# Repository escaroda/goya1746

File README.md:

<div>
  <picture>
    <source media="(prefers-color-scheme: light)" srcset="docs/logo_terein_light.svg">
    
  </picture>
</div>

## Overview

**goya1746** is an overdrive & preamp pedal based on the legendary Diezel VH4 channel 3. Fully open circuit board designed in KiCad 8. The main idea was to avoid oscillations on all gain levels. This project is shared for hobbyists who want to study, modify, or build their own. The full PCB outline is 115 × 70 mm (4.53 × 2.76 in), but the usable area is about 96 × 70 mm (3.78 × 2.76 in) if you remove the side "wings" in KiCad and define your own edge cut before generating Gerbers. In theory, it should fit a 1590BB enclosure, but keep in mind that each potentiometer is wired separately and the connection pads are not located at the corners of the PCB, so there will be quite a lot of wiring inside.

## Manufacturing

Check [Releases](https://github.com/escaroda/goya1746/releases) page for `.zip` Gerber files ready for production.
If you want to fabricate the PCB, just upload the `.zip` Gerber files to your favorite board house (e.g. JLCPCB, PCBWay, NEXTPCB). Make sure you can source all components in the correct form factor before manufacturing the board.

## Important notes

- This pedal should be powered with 12-18VDC. Power draw 100mA. There are claims that 15VDC provides the best results because it generates less heat in the voltage regulator, but 18VDC is the standard.
- The LM2940 regulator is installed vertically. Its metal tab can be mounted to the chassis to help dissipate heat — just make sure the chassis is grounded and not connected to any other signal paths. This workaround increases build complexity and will be refined in a future revision. The goal was to minimize board temperature to prolong the lifespan of nearby electrolytic capacitors.
- Only five electrolytic capacitors are used, and they are strategically placed to provide shielding for the TC1044SCPA charge pump switching regulator IC from nearby components.
- Some capacitors, specifically C3, C4, C5, C9, C12, C17, C18, C20 and C22, that were originally electrolytic, have been replaced with film capacitors. The schematic remains unchanged, but the PCB footprints are different. You can still install electrolytic capacitors in those positions, but be sure to observe the correct polarity. Future revisions will return to electrolytic capacitors because they're cheaper and the experiment didn't produce a better tone.
- The resistor 2.2K 1/4W for the LED 12V should be placed on the wire that connects it to the PCB. Adjust the resistor value to achieve the desired brightness.
- Even though the LM2940CT-12/NOPB voltage regulator provides reverse-polarity protection for the entire circuit, it is still good practice to solder a 1N5817 Schottky diode in series with the + wire leading to the DC input. The striped end (cathode) should face the PCB. For example: DC Jack → [Anode — Diode — Cathode] → PCB. You can see this approach used in almost all PedalPCB schematics. Make sure you identify the +V and Ground pins of the DC input by referring to the PCB design in KiCad.
- For experimental purposes, the mid-pot tone control is wired in the so-called "Marshall style," which gives the mid control a stronger effect and shifts the tone toward a punchier, more mid-rich sound compared to a "Fender style" tone stack. To switch back to the "Fender style" configuration, connect pins 2 and 3 of the MID potentiometer together.
- Because of space limitations in this version, buffered bypass solder pads are not included. This may be added in a future revision. At the moment, the on/off switch must be wired as a true bypass by the builder. Or, if you're feeling hacky, you can connect a wire between the C3 capacitor and the R4 resistor (for example, to the side of the R4 resistor that isn't connected to Ground), and that will be your buffer. And the signal after R17 should be shorted to Ground during bypass.

P.S. Future releases are not expected in the near term due to financial constraints. However, once the situation improves, development will continue, including projects such as Turbo Rat, SansAmp GT-2, Boss CE-2, as well as a search for the best fuzz circuit.

## Acknowledgments

- [Diezel](https://www.diezelamplification.com/artist/) for inspiring design of modern high-gain amplifiers.
- [freestompboxes.org](https://www.freestompboxes.org/viewtopic.php?t=28011) and its community — without their prior work, this project would not have been possible.
- [pedalpcb.com](https://www.pedalpcb.com/product/valhalla/) DIY shop, for inspiration and clear, easy-to-understand schematics.
- [aionfx.com](https://aionfx.com/project/dz4-preamp/) for showing how things can be changed.
- [pcbguitarmania.com](https://pcbguitarmania.com/product/benzin-vh4/) for yet another reference and food for thoughts.
- [effectslayouts.blogspot.com](https://effectslayouts.blogspot.com/2019/07/diezel-vh4.html) for better understanding how the footswitch wiring should work.
- [techexplorations.com](https://techexplorations.com/kicad/) for great KiCad educational materials.
- [Hans Rosenberg](https://www.youtube.com/@HansRosenberg74/videos) for interesting talks about good PCB design in general.

## Guides

These guides might help beginners who have never built their own pedals. Some links might become broken.

- [Gray Bench Electronics - Full Kit Build Video](https://www.youtube.com/watch?v=_JjrbrLn0x4)
- [RUDE TECH - Guitar Effect Pedal Kit Build Instructions Video](https://www.youtube.com/watch?v=ZrMTKuxQ1Xw)
- [pedalparts.co.uk - General Build Guide PDF](https://pedalparts.co.uk/docs/GeneralBuildGuide.pdf)
- [five-cats-pedals.co.uk - General Build Guide PDF](https://www.five-cats-pedals.co.uk/wp-content/uploads/2022/09/FiveCatsPedals-General-Build-Guide-V1.1-Aug-2022.pdf)
- [aionfx.com - Troubleshooting Guide PDF](https://aionfx.com/app/files/docs/kit_troubleshooting_guide.pdf)
- [masfx.io - A Guide to Build Your Own DIY Guitar Pedal PDF](https://masfx.io/quickfuzz.pdf)
- [guitarpcb.com - A Beginner's Guide to Effects Pedals Components PDF](https://guitarpcb.com/wp-content/uploads/2018/07/A-Beginners-Guide-to-Components.pdf)
- [premierguitar.com - Build Your Own Stompbox PDF](https://roar-assets-auto.rbl.ms/documents/9051/Oct14_PGDistortion_BuildGuide_Final_R2.pdf)

## Bill of Materials

All resistors are 1/4 W metal film with 1% tolerance. All capacitors must have a minimum voltage rating of 35 V. Consider capacitors to be polypropylene film unless otherwise specified. If 25 kΩ potentiometers are unavailable, a 50 kΩ potentiometer may be used together with a 50 kΩ resistor in parallel. This changes the taper slightly (especially for log pots), because the resistance curve is altered by the parallel resistor. Ferrite bead R1 is optional and can be replaced with a wire link. The OPA2134 at U1 may be substituted with another TL072 without any noticeable difference.

You'll also need:
- 6.3 mm jack sockets,
- DIP8 sockets for each op-amp and a charge pump,
- optional JST connectors for DC input and LED,
- a **plastic** DC input jack wired for center negative.

This pedal provides two output options: Guitar Out and Power Out. In most cases, you won't need to wire both. If the pedal is used at the end of a signal chain (similar to a real amplifier), Power Out is the preferred choice. Power Out is a low-impedance, line-level signal, so it can be safely connected to standard line inputs, such as those on audio interface. Guitar Out is a traditional high-impedance output suitable for connecting to other pedals or amp inputs.

*For ICs and other essential components, use reputable suppliers only. Avoid sources like eBay or AliExpress, as counterfeit or unreliable parts are widespread on those platforms and may cause malfunction or failure.*

|Reference          |Value           |Qty|Notes                                           |
|-------------------|----------------|---|------------------------------------------------|
|BASS1              |A1M             |1  |                                                |
|C1,C7,C15,C16      |22n             |4  |                                                |
|C2,C6,C13          |100p            |3  |Ceramic Disc                                    |
|C3,C4,C5,C17       |1u              |4  |                                                |
|C8                 |2n2             |1  |                                                |
|C23                |2n2             |1  |Ceramic Disc or Film                            |
|C9,C12,C18         |2u2             |3  |                                                |
|C10                |47p             |1  |Ceramic Disc                                    |
|C11                |4n7             |1  |                                                |
|C14                |560p            |1  |Ceramic Disc                                    |
|C19                |330n            |1  |                                                |
|C20,C22            |10u             |2  |                                                |
|C21                |1n              |1  |Ceramic Disc or Film                            |
|C24,C25,C26,C27,C28|47u             |5  |Electrolytic ~35V                               |
|D1,D2,D5,D6        |1N4148          |4  |Signal diode, DO-35                             |
|D3,D4              |1N4734A         |2  |5.6V zener (equivalents: 1N752, 1N5232), DO-41  |
|D7                 |LED 12V         |1  |Require ~2.2K resistor                          |
|J1                 |GUITAR INPUT    |1  |                                                |
|J2                 |DC INPUT        |1  |                                                |
|J3                 |POWER OUT       |1  |                                                |
|J4                 |GUITAR OUT      |1  |                                                |
|R1                 |FerriteBead     |1  |Optional                                        |
|R2,R3,R14          |1M              |3  |                                                |
|R4,R5,R15,R25,R37  |100K            |5  |                                                |
|R6,R13,R18,R33     |10K             |4  |                                                |
|R7,R10,R11,R17,R19 |220K            |5  |                                                |
|R8,R16             |470K            |2  |                                                |
|R9                 |680K            |1  |                                                |
|R20                |39K             |1  |                                                |
|R24                |1M5             |1  |                                                |
|R26,R34            |1K              |2  |                                                |
|R28                |100R            |1  |                                                |
|R30                |47R             |1  |                                                |
|R31                |56K             |1  |                                                |
|R32                |4K7             |1  |                                                |
|R36                |150K            |1  |                                                |
|R38,R39            |10R             |2  |                                                |
|U1                 |OPA2134         |1  |Dual op-amp, DIP8. May be substituted with TL072|
|U2,U3              |TL072           |2  |Dual op-amp, DIP8                               |
|IC4                |LM2940CT-12_NOPB|1  |Low-dropout voltage regulator +12V              |
|IC100              |TC1044SCPA      |1  |Charge Pump IC, DIP8                            |
|DEEP1,PRES1        |C25K            |2  |                                                |
|GAIN1              |A250K           |1  |                                                |
|MID1               |B25K            |1  |                                                |
|TREBLE1            |B250K           |1  |                                                |
|VOL1               |A10K            |1  |                                                |

## Ground & Shielding

The chassis should be properly grounded to ensure effective shielding and noise reduction. Where possible, use cables with an outer braided shield and connect the shield to ground at least on one end — preferably at the PCB side. The metal backs of potentiometers may also be connected to ground to help reduce noise pickup through their housings. Ground loops are generally not a concern inside a small enclosure such as a pedal, so a strict star-ground topology is unnecessary. The **DC input jack must be plastic** (isolated from the enclosure). Most pedals use a negative center power supply, so a metal jack touching the chassis could short the positive voltage to ground.

As a side note. There are a lot of myths and misconceptions about grounding in PCB design, mostly because of the many variables that need to be considered together with each statement. At some point, you think you understand how it works, but then you realize you don't. It's not always clear what the real cause of a problem is, and fixing one issue can accidentally fix another, leading to false conclusions.

For example, advanced grounding techniques are mainly used for high-frequency applications, and the effects are often negligible in the audio range (up to 20 kHz). Through-hole components are considered obsolete for high-frequency PCBs, yet they are abundant in most analog music equipment. If we start replacing everything with SMD components, we might lose some of the unique characteristics that contribute to the sound we expect, or just our own perception might change.

And let's not forget that the sound we're looking for doesn't always have to be perfect — it just has to be pleasant to our ears. Who wants to listen to a perfectly clean sine wave, right? We enjoy it when it's mixed with other harmonics and subtle modulations that make the sound feel alive. Often, it's exactly those imperfections in the components and PCB layout that create the desired effect.

## PCB Specifications

- Layers: 2
- Thickness: 1.6 mm
- PCB Size: 115 x 70 mm (4.53 × 2.76 in)
- Copper weight: 1 oz (default PCB fab)
- Trace clearance: 6 mil or 0.1524mm
- Soldermask: [Black / Green / Anything]
- Silkscreen: [White]
- Surface finish: HASL
- Material: FR-4
- Via finish: Tented
- Min. Drill Hole: 0.3 mm
- Assembly: Through-hole components only (no SMD)

## Recommended Fabricators
- NEXTPCB
- JLCPCB
- PCBWay

## Gallery

## TODO

- Add a connection pad for the buffered output between C3 and R4, and find a suitable location for it on the PCB. Add a connection pad after R17 to be able to short it to Ground during bypass. Update schematic.
- Make configuration where all caps are the same type as in Diezel VH4 pedal since any difference could affect the tone.
- Add + signs on a silkscreen layer for all connection pads to lower the risk of mistakes.
- Position the voltage regulator so that it can be laid flat on the PCB. Add a ground plane underneath it for better heat distribution.
- Consider adapting the PCB layout to fit more popular enclosures, such as 1590BB.
- Would it be possible to rewire everything so that pots connected directly to the PCB? Estimate PCB size, production costs and a headache of acquiring the correct pots.

## License

This hardware design is distributed under the MIT License.
Copyright (c) 2025 Dmitry Escaroda.

## Contribution

If you build this pedal, feel free to share photos or mods via Discussions. If you are an experienced Electronics Engineer or PCB Designer and see how something could be improved for the benefit of all, please submit an issue.

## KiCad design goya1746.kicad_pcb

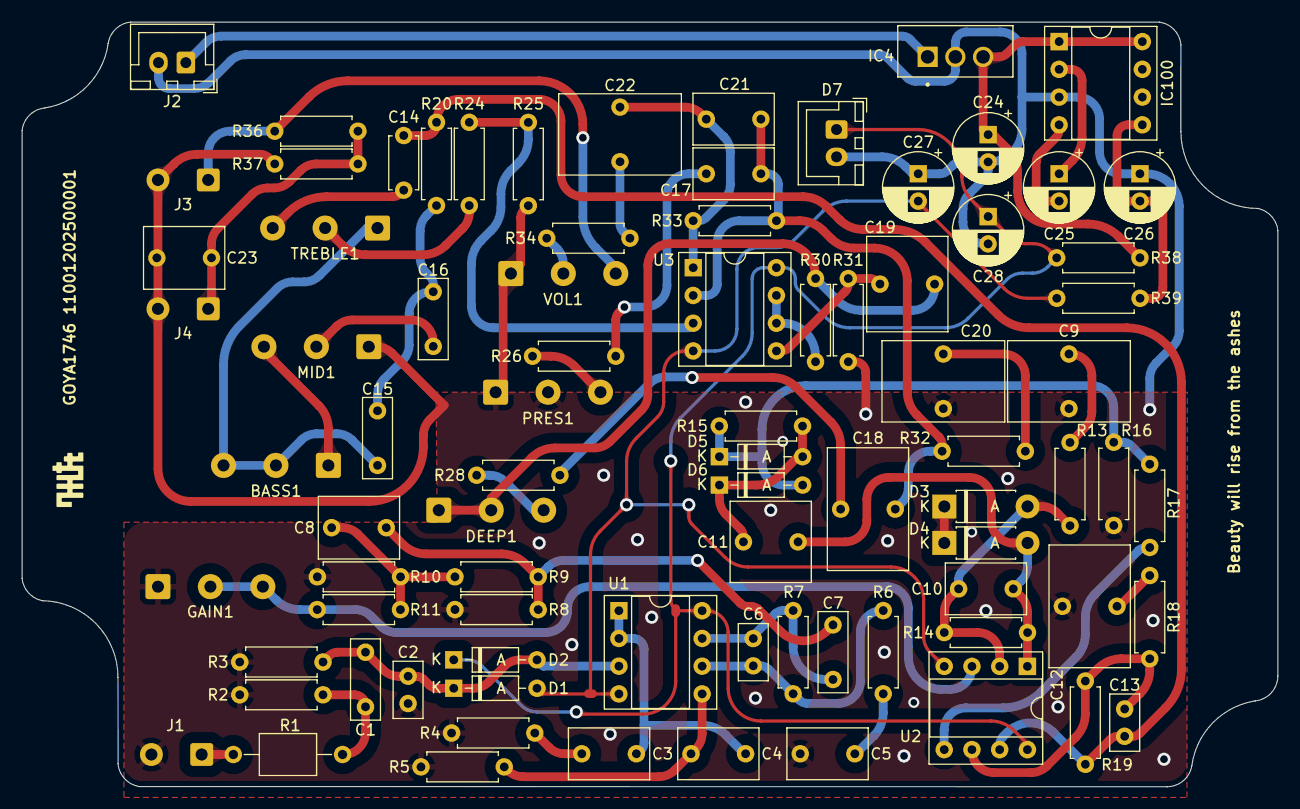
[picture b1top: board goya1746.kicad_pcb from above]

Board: 2 copper layers, 115.0 x 70.0 mm, 83 parts (0 on the bottom side), 51 nets.

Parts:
BASS1: A1M; SolderWire-0.5sqmm_1x03_P4.8mm_D0.9mm_OD2.3mm
C1, C7, C15, C16: 22n; C_Rect_L7.2mm_W2.5mm_P5.00mm_FKS2_FKP2_MKS2_MKP2
C2, C6, C13: 100p; C_Disc_D5.0mm_W2.5mm_P2.50mm
C3, C4, C5, C17: 1u; C_Rect_L7.2mm_W4.5mm_P5.00mm_FKS2_FKP2_MKS2_MKP2
C8, C23: 2n2; C_Rect_L7.2mm_W5.5mm_P5.00mm_FKS2_FKP2_MKS2_MKP2
C9, C12, C18: 2u2; C_Rect_L7.2mm_W11.0mm_P5.00mm_FKS2_FKP2_MKS2_MKP2
C10: 47p; C_Rect_L7.2mm_W4.5mm_P5.00mm_FKS2_FKP2_MKS2_MKP2
C11: 4n7; C_Rect_L7.2mm_W7.2mm_P5.00mm_FKS2_FKP2_MKS2_MKP2
C14: 560p; C_Disc_D4.7mm_W2.5mm_P5.00mm
C19: 330n; C_Rect_L7.2mm_W8.5mm_P5.00mm_FKP2_FKP2_MKS2_MKP2
C20, C22: 10u; C_Rect_L7.2mm_W11.0mm_P5.00mm_FKS2_FKP2_MKS2_MKP2
C21: 1n; C_Rect_L7.2mm_W4.5mm_P5.00mm_FKS2_FKP2_MKS2_MKP2
C24, C25, C26, C27, C28: 47u; CP_Radial_D6.3mm_P2.50mm
D1, D2, D5, D6: 1N4148; D_DO-35_SOD27_P7.62mm_Horizontal
D3, D4: 1N4734A; D_DO-41_SOD81_P7.62mm_Horizontal
D7: LED 12V; JST_XH_B2B-XH-A_1x02_P2.50mm_Vertical
DEEP1: C25K; SolderWire-0.5sqmm_1x03_P4.8mm_D0.9mm_OD2.3mm
GAIN1: A250K; SolderWire-0.5sqmm_1x03_P4.8mm_D0.9mm_OD2.3mm
IC4: LM2940CT-12_NOPB; TO254P1054X470X1955-3
IC100: TC1044SCPA; DIP-8_W7.62mm_Socket
J1: GUITAR INPUT; SolderWire-0.5sqmm_1x02_P4.6mm_D0.9mm_OD2.1mm
J2: DC INPUT; JST_XH_B2B-XH-A_1x02_P2.50mm_Vertical
J3: POWER OUT; SolderWire-0.5sqmm_1x02_P4.6mm_D0.9mm_OD2.1mm
J4: GUITAR OUT; SolderWire-0.5sqmm_1x02_P4.6mm_D0.9mm_OD2.1mm
MID1: B25K; SolderWire-0.5sqmm_1x03_P4.8mm_D0.9mm_OD2.3mm
PRES1: C25K; SolderWire-0.5sqmm_1x03_P4.8mm_D0.9mm_OD2.3mm
R1: FerriteBead; L_Axial_L5.0mm_D3.6mm_P10.00mm_Horizontal_Murata_BL01RN1A2A2
R2, R3, R14: 1M; R_Axial_DIN0207_L6.3mm_D2.5mm_P7.62mm_Horizontal
R4, R5, R15, R25, R37: 100K; R_Axial_DIN0207_L6.3mm_D2.5mm_P7.62mm_Horizontal
R6, R13, R18, R33: 10K; R_Axial_DIN0207_L6.3mm_D2.5mm_P7.62mm_Horizontal
R7, R10, R11, R17, R19: 220K; R_Axial_DIN0207_L6.3mm_D2.5mm_P7.62mm_Horizontal
R8, R16: 470K; R_Axial_DIN0207_L6.3mm_D2.5mm_P7.62mm_Horizontal
R9: 680K; R_Axial_DIN0207_L6.3mm_D2.5mm_P7.62mm_Horizontal
R20: 39K; R_Axial_DIN0207_L6.3mm_D2.5mm_P7.62mm_Horizontal
R24: 1M5; R_Axial_DIN0207_L6.3mm_D2.5mm_P7.62mm_Horizontal
R26, R34: 1K; R_Axial_DIN0207_L6.3mm_D2.5mm_P7.62mm_Horizontal
R28: 100R; R_Axial_DIN0207_L6.3mm_D2.5mm_P7.62mm_Horizontal
R30: 47R; R_Axial_DIN0207_L6.3mm_D2.5mm_P7.62mm_Horizontal
R31: 56K; R_Axial_DIN0207_L6.3mm_D2.5mm_P7.62mm_Horizontal
R32: 4K7; R_Axial_DIN0207_L6.3mm_D2.5mm_P7.62mm_Horizontal
R36: 150K; R_Axial_DIN0207_L6.3mm_D2.5mm_P7.62mm_Horizontal
R38, R39: 10R; R_Axial_DIN0207_L6.3mm_D2.5mm_P7.62mm_Horizontal
TREBLE1: B250K; SolderWire-0.5sqmm_1x03_P4.8mm_D0.9mm_OD2.3mm
U1: OPA2134; DIP-8_W7.62mm_Socket
U2, U3: TL072; DIP-8_W7.62mm_Socket
VOL1: A10K; SolderWire-0.5sqmm_1x03_P4.8mm_D0.9mm_OD2.3mm

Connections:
+12V: C28.1, D2.1 (K), D7.1, R38.1, U1.8 (V+), U2.8 (V+), U3.8 (V+)
-12V: C27.2, D1.2 (A), R39.1, U1.4 (V-), U2.4 (V-), U3.4 (V-)
GND: C2.1, C5.2, C9.2, C12.2, C20.2, C23.2, C24.2, C26.1, C27.1, C28.2, D7.2, GAIN1.1, IC4.2 (GND), IC100.3 (GND), J1.2, J2.2, J3.2, J4.2, MID1.1, PRES1.1, PRES1.2, R2.2, R3.2, R4.2, R5.2, R8.2, R10.2, R16.1, R25.1, R31.1, R37.1, VOL1.1
unnamed: BASS1.1, MID1.3
unnamed: BASS1.2, BASS1.3, C15.1, TREBLE1.1
unnamed: C1.1, R1.2, R2.1
unnamed: C3.2, R4.1
unnamed: C5.1, R6.1
unnamed: C6.1, C7.2, R7.2, U1.7
unnamed: C7.1, C8.2, R8.1, R9.1
unnamed: C8.1, R9.2, R10.1, R11.1
unnamed: C9.1, R13.1
unnamed: C12.1, R18.2
unnamed: C13.1, C14.2, R19.1, R20.1, U2.7
unnamed: C14.1, TREBLE1.3
unnamed: C15.2, C16.2, R20.2
unnamed: C16.1, MID1.2
unnamed: C17.2, R26.2
unnamed: C18.2, R28.1
unnamed: C19.1, DEEP1.1, DEEP1.2, R30.2
unnamed: C20.1, R32.2
unnamed: C21.1, C22.1, R33.1, U3.1
unnamed: C22.2, R34.1
unnamed: C1.2, C2.2, D1.1 (K), D2.2 (A), R3.1, U1.3 (+)
unnamed: C10.2, D3.2 (A), R13.2, R14.1, U2.2 (-)
unnamed: D3.1 (K), D4.1 (K)
unnamed: C10.1, C11.2, D4.2 (A), R14.2, U2.1
unnamed: C11.1, D5.2 (A), D6.1 (K), R15.1
unnamed: D5.1 (K), D6.2 (A), R15.2, R16.2, R17.2
unnamed: DEEP1.3, R28.2
unnamed: IC4.1 (IN), J2.1
unnamed: C24.1, IC4.3 (OUT), IC100.1 (BOOST), IC100.8 (V+), R38.2
unnamed: C25.1, IC100.2 (CAP+)
unnamed: C25.2, IC100.4 (CAP-)
unnamed: C26.2, IC100.5 (VOUT), R39.2
unnamed: J1.1, R1.1
unnamed: J3.1, R36.1, VOL1.3
unnamed: C23.1, J4.1, R36.2, R37.2
unnamed: PRES1.3, R26.1
unnamed: R24.1, TREBLE1.2
unnamed: R34.2, VOL1.2
unnamed: C3.1, C4.1, U1.1, U1.2 (-)
unnamed: C4.2, R5.1, U1.5 (+)
unnamed: C6.2, R6.2, R7.1, U1.6 (-)
unnamed: GAIN1.2, GAIN1.3, R11.2, U2.3 (+)
unnamed: R17.1, U2.5 (+)
unnamed: C13.2, R18.1, R19.2, U2.6 (-)
unnamed: R24.2, R25.2, U3.3 (+)
unnamed: C17.1, C18.1, C21.2, R32.1, R33.2, U3.2 (-)
unnamed: C19.2, R31.2, U3.5 (+)
unnamed: R30.1, U3.6 (-), U3.7

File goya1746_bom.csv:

Reference	Value	Datasheet	Footprint	Qty	DNP
BASS1	A1M	~	Connector_Wire:SolderWire-0.5sqmm_1x03_P4.8mm_D0.9mm_OD2.3mm	1	
C1,C7,C15,C16	22n	~	Capacitor_THT:C_Rect_L7.2mm_W2.5mm_P5.00mm_FKS2_FKP2_MKS2_MKP2	4	
C2,C6,C13	100p	~	Capacitor_THT:C_Disc_D5.0mm_W2.5mm_P2.50mm	3	
C3,C4,C5,C17	1u	~	Capacitor_THT:C_Rect_L7.2mm_W4.5mm_P5.00mm_FKS2_FKP2_MKS2_MKP2	4	
C8,C23	2n2	~	Capacitor_THT:C_Rect_L7.2mm_W5.5mm_P5.00mm_FKS2_FKP2_MKS2_MKP2	2	
C9,C12,C18	2u2	~	Capacitor_THT:C_Rect_L7.2mm_W11.0mm_P5.00mm_FKS2_FKP2_MKS2_MKP2	3	
C10	47p	~	Capacitor_THT:C_Rect_L7.2mm_W4.5mm_P5.00mm_FKS2_FKP2_MKS2_MKP2	1	
C11	4n7	~	Capacitor_THT:C_Rect_L7.2mm_W7.2mm_P5.00mm_FKS2_FKP2_MKS2_MKP2	1	
C14	560p	~	Capacitor_THT:C_Disc_D4.7mm_W2.5mm_P5.00mm	1	
C19	330n	~	Capacitor_THT:C_Rect_L7.2mm_W8.5mm_P5.00mm_FKP2_FKP2_MKS2_MKP2	1	
C20,C22	10u	~	Capacitor_THT:C_Rect_L7.2mm_W11.0mm_P5.00mm_FKS2_FKP2_MKS2_MKP2	2	
C21	1n	~	Capacitor_THT:C_Rect_L7.2mm_W4.5mm_P5.00mm_FKS2_FKP2_MKS2_MKP2	1	
C24,C25,C26,C27,C28	47u	~	Capacitor_THT:CP_Radial_D6.3mm_P2.50mm	5	
D1,D2,D5,D6	1N4148	~	Diode_THT:D_DO-35_SOD27_P7.62mm_Horizontal	4	
D3,D4	1N4734A	~	Diode_THT:D_DO-41_SOD81_P7.62mm_Horizontal	2	
D7	LED 12V	~	Connector_JST:JST_XH_B2B-XH-A_1x02_P2.50mm_Vertical	1	
DEEP1,PRES1	C25K	~	Connector_Wire:SolderWire-0.5sqmm_1x03_P4.8mm_D0.9mm_OD2.3mm	2	
GAIN1	A250K	~	Connector_Wire:SolderWire-0.5sqmm_1x03_P4.8mm_D0.9mm_OD2.3mm	1	
IC4	LM2940CT-12_NOPB		LM2940CT12NOPB:TO254P1054X470X1955-3	1	
IC100	TC1044SCPA		Package_DIP:DIP-8_W7.62mm_Socket	1	
J1	GUITAR INPUT	~	Connector_Wire:SolderWire-0.5sqmm_1x02_P4.6mm_D0.9mm_OD2.1mm	1	
J2	DC INPUT	~	Connector_JST:JST_XH_B2B-XH-A_1x02_P2.50mm_Vertical	1	
J3	POWER OUT	~	Connector_Wire:SolderWire-0.5sqmm_1x02_P4.6mm_D0.9mm_OD2.1mm	1	
J4	GUITAR OUT	~	Connector_Wire:SolderWire-0.5sqmm_1x02_P4.6mm_D0.9mm_OD2.1mm	1	
MID1	B25K	~	Connector_Wire:SolderWire-0.5sqmm_1x03_P4.8mm_D0.9mm_OD2.3mm	1	
R1	FerriteBead	~	Inductor_THT:L_Axial_L5.0mm_D3.6mm_P10.00mm_Horizontal_Murata_BL01RN1A2A2	1	
R2,R3,R14	1M	~	Resistor_THT:R_Axial_DIN0207_L6.3mm_D2.5mm_P7.62mm_Horizontal	3	
R4,R5,R15,R25,R37	100K	~	Resistor_THT:R_Axial_DIN0207_L6.3mm_D2.5mm_P7.62mm_Horizontal	5	
R6,R13,R18,R33	10K	~	Resistor_THT:R_Axial_DIN0207_L6.3mm_D2.5mm_P7.62mm_Horizontal	4	
R7,R10,R11,R17,R19	220K	~	Resistor_THT:R_Axial_DIN0207_L6.3mm_D2.5mm_P7.62mm_Horizontal	5	
R8,R16	470K	~	Resistor_THT:R_Axial_DIN0207_L6.3mm_D2.5mm_P7.62mm_Horizontal	2	
R9	680K	~	Resistor_THT:R_Axial_DIN0207_L6.3mm_D2.5mm_P7.62mm_Horizontal	1	
R20	39K	~	Resistor_THT:R_Axial_DIN0207_L6.3mm_D2.5mm_P7.62mm_Horizontal	1	
R24	1M5	~	Resistor_THT:R_Axial_DIN0207_L6.3mm_D2.5mm_P7.62mm_Horizontal	1	
R26,R34	1K	~	Resistor_THT:R_Axial_DIN0207_L6.3mm_D2.5mm_P7.62mm_Horizontal	2	
R28	100R	~	Resistor_THT:R_Axial_DIN0207_L6.3mm_D2.5mm_P7.62mm_Horizontal	1	
R30	47R	~	Resistor_THT:R_Axial_DIN0207_L6.3mm_D2.5mm_P7.62mm_Horizontal	1	
R31	56K	~	Resistor_THT:R_Axial_DIN0207_L6.3mm_D2.5mm_P7.62mm_Horizontal	1	
R32	4K7	~	Resistor_THT:R_Axial_DIN0207_L6.3mm_D2.5mm_P7.62mm_Horizontal	1	
R36	150K	~	Resistor_THT:R_Axial_DIN0207_L6.3mm_D2.5mm_P7.62mm_Horizontal	1	
R38,R39	10R	~	Resistor_THT:R_Axial_DIN0207_L6.3mm_D2.5mm_P7.62mm_Horizontal	2	
TREBLE1	B250K	~	Connector_Wire:SolderWire-0.5sqmm_1x03_P4.8mm_D0.9mm_OD2.3mm	1	
U1	OPA2134	http://www.ti.com/lit/ds/symlink/opa134.pdf	Package_DIP:DIP-8_W7.62mm_Socket	1	
U2,U3	TL072	http://www.ti.com/lit/ds/symlink/tl071.pdf	Package_DIP:DIP-8_W7.62mm_Socket	2	
VOL1	A10K	~	Connector_Wire:SolderWire-0.5sqmm_1x03_P4.8mm_D0.9mm_OD2.3mm	1

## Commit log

2025-10-24 Init
2025-10-24 Fix Readme
2025-10-25 Readme adjustments
2025-10-25 Added zener diode note
2025-10-25 KiCad education material mentioning
2025-10-25 BOM adjustments
2025-10-26 BOM list adjustments
2025-10-27 Add dimension in inches
2025-10-28 Readme TODO
2025-10-28 TODO adjustments
2025-10-29 Add Guides
2025-10-30 Add datasheets
2025-10-30 Readme Guides adjustments
2025-11-20 README caps adjustments
2025-11-20 Updated KiCAD v9.0.6. README caps adjustments, updated schematic with buffer and footswich outputs (out of sync with pcb design = not production ready)
